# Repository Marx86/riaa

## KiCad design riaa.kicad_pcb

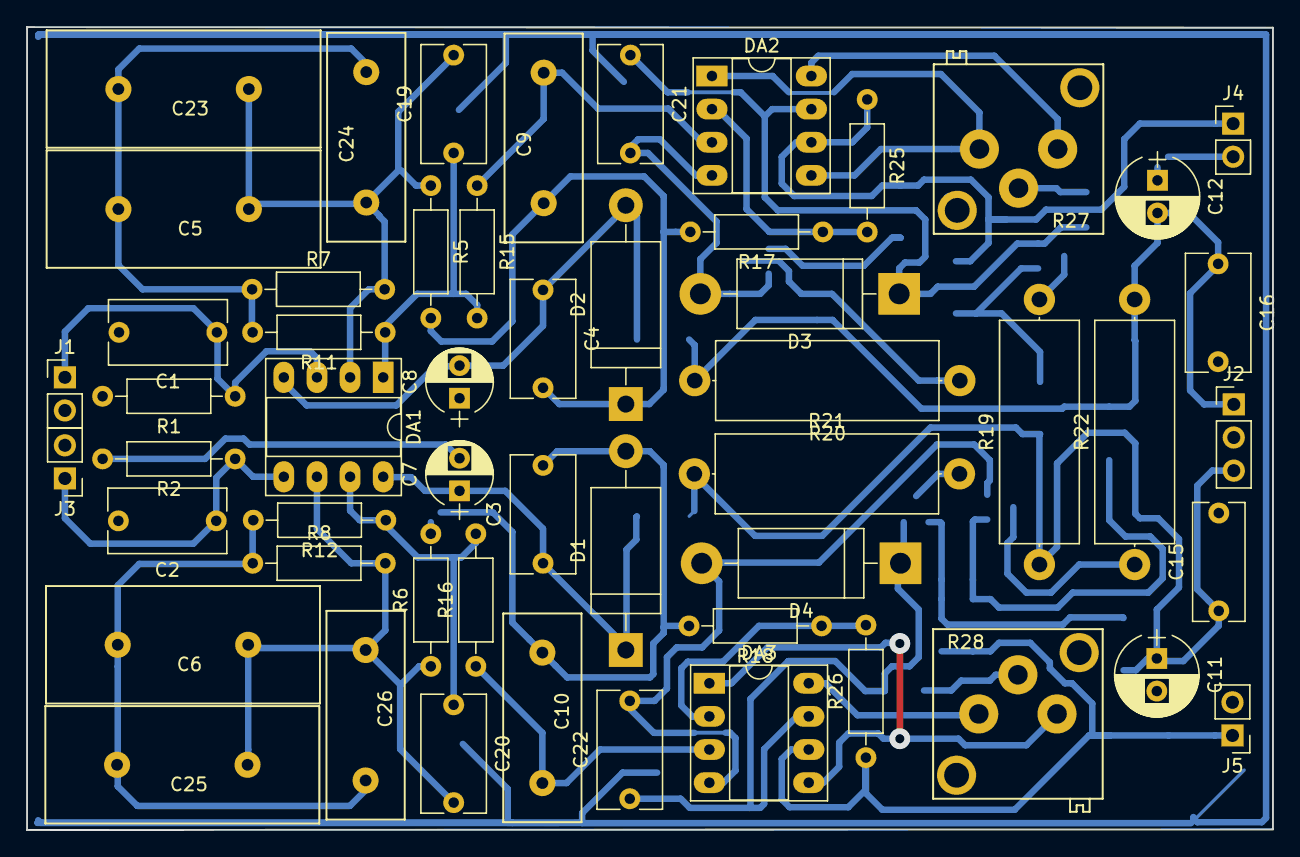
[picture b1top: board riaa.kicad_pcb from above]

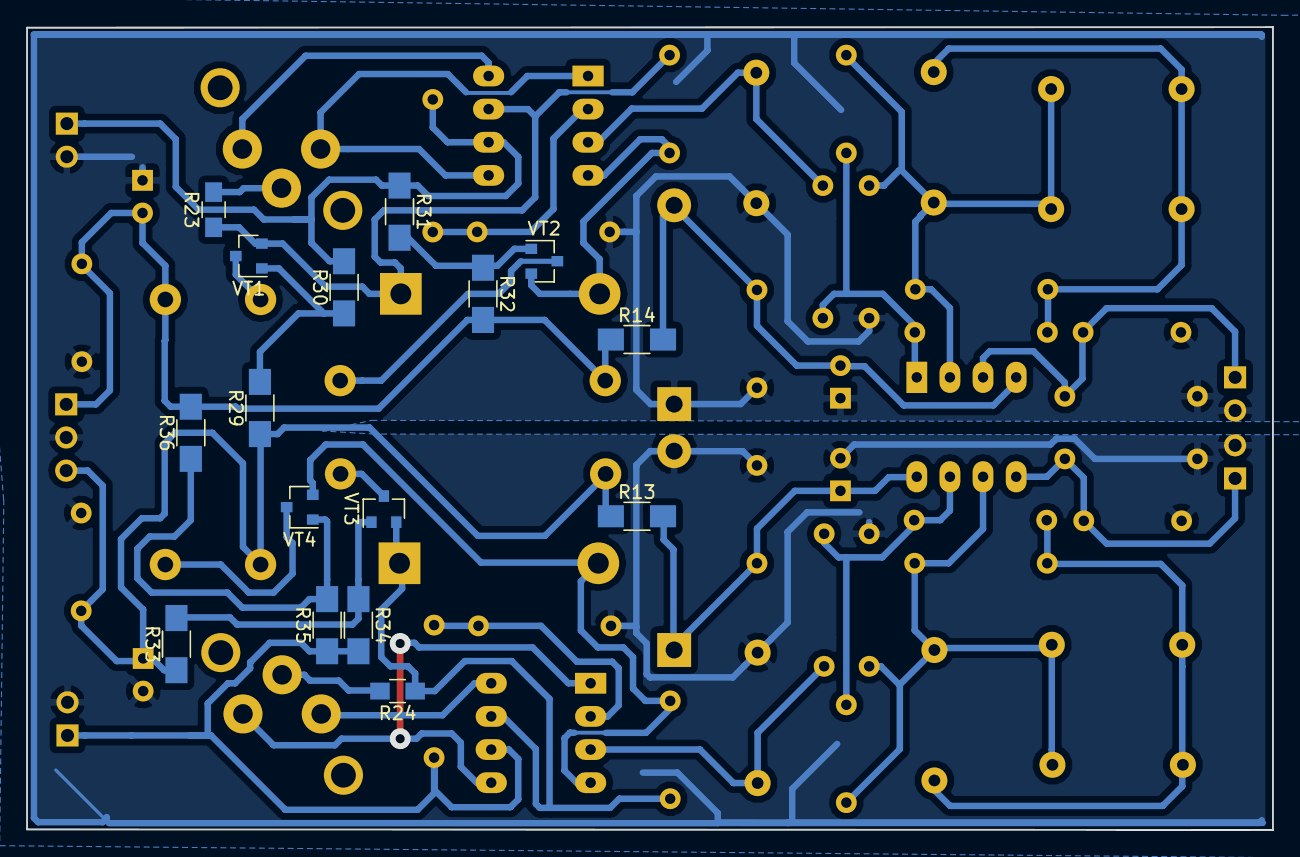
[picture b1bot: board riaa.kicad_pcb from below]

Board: 2 copper layers, 95.5 x 61.5 mm, 70 parts (16 on the bottom side), 37 nets.

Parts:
C1, C2: 200p; C_Rect_L9.0mm_W4.9mm_P7.50mm_MKT
C3, C4, C16, C21, C22: 0.1; C_Rect_L9.0mm_W4.9mm_P7.50mm_MKT
C5, C23, C25: 30.1n; k71-7_21x9_mm
C6: 30.2n; k71-7_21x9_mm
C7, C8: 2.2; CP_Radial_D5.0mm_P2.50mm
C9, C10: 10.75n; k71-7_16x6_mm
C11, C12: 2.2; CP_Radial_D6.3mm_P2.50mm
C15: 0.1; C_Rect_L9.0mm_W3.9mm_P7.50mm_MKT
C19, C20: 110; C_Rect_L9.0mm_W4.9mm_P7.50mm_MKT
C24, C26: 6510; k71-7_16x6_mm
D1, D2: КС518; D_DO-201_P15.24mm_Horizontal
D3, D4: 1N5364; D_DO-201AD_P15.24mm_Horizontal
DA1: OPA2132; DIP-8_W7.62mm_Socket_LongPads
DA2, DA3: AD845; DIP-8_W7.62mm_Socket_LongPads
J1, J3: IN; Pin_Header_Straight_1x02_Pitch2.54mm
J2: POWER; Pin_Header_Straight_1x03_Pitch2.54mm
J4, J5: OUT; Pin_Header_Straight_1x02_Pitch2.54mm
R1, R2: 47k; R_Axial_DIN0207_L6.3mm_D2.5mm_P10.16mm_Horizontal
R5, R6: 205; R_Axial_DIN0207_L6.3mm_D2.5mm_P10.16mm_Horizontal
R7, R8: 47.5k; R_Axial_DIN0207_L6.3mm_D2.5mm_P10.16mm_Horizontal
R11, R12: 5.11k; R_Axial_DIN0207_L6.3mm_D2.5mm_P10.16mm_Horizontal
R13, R14: 3.6k; R_1206_HandSoldering
R15, R16: 6.98k; R_Axial_DIN0207_L6.3mm_D2.5mm_P10.16mm_Horizontal
R17, R18: 10k; R_Axial_DIN0207_L6.3mm_D2.5mm_P10.16mm_Horizontal
R19, R20, R21, R22: 1.2k; R_Axial_DIN0617_L17.0mm_D6.0mm_P20.32mm_Horizontal
R23, R24: 390; R_0805_HandSoldering
R25, R26: 30k; R_Axial_DIN0207_L6.3mm_D2.5mm_P10.16mm_Horizontal
R27, R28: 1k; c5-2
R29, R32, R33, R36: 100k; R_1206_HandSoldering
R30, R31, R34, R35: 62k; R_1206_HandSoldering
VT1, VT3: MMBT5551; SOT-23
VT2, VT4: MMBT5401; SOT-23

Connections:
GNDA: C1.2, C2.2, C3.2, C4.2, C7.2, C8.1, C9.2, C10.2, C11.2, C12.1, C15.2, C16.2, D1.2, D2.1, J1.2, J2.2, J3.2, J4.2, J5.2, R1.2, R2.2, R5.2, R6.2, R17.2, R18.2
unnamed: C1.1, DA1.3, J1.1, R1.1
unnamed: C2.1, DA1.5, J3.1, R2.1
unnamed: C3.1, C7.1, D1.1, DA1.8, R13.2
unnamed: C4.1, C8.2, D2.2, DA1.4, R14.2
unnamed: C9.1, DA2.3, R15.1
unnamed: C10.1, DA3.3, R16.1
unnamed: C19.1, DA1.1, R11.1, R15.2
unnamed: C5.2, C19.2, C23.2, C24.2, DA1.2, R5.1, R7.2
unnamed: C20.1, DA1.7, R12.1, R16.2
unnamed: C6.2, C20.2, C25.2, C26.2, DA1.6, R6.1, R8.2
unnamed: C21.1, D3.1, DA2.7, R23.1, VT1.2
unnamed: C21.2, D3.2, DA2.4, VT2.2
unnamed: C22.1, D4.1, DA3.7, R24.1, VT3.2
unnamed: C22.2, D4.2, DA3.4, VT4.2
unnamed: C5.1, C23.1, C24.1, R7.1, R11.2
unnamed: C6.1, C25.1, C26.1, R8.1, R12.2
unnamed: DA2.1, DA2.5, R27.3
unnamed: DA2.2, R17.1, R25.2
unnamed: DA2.6, J4.1, R25.1, R30.2, R31.1
unnamed: DA2.8, R27.1
unnamed: DA3.1, DA3.5, R28.3
unnamed: DA3.2, R18.1, R26.2
unnamed: DA3.6, J5.1, R26.1, R34.2, R35.1
unnamed: DA3.8, R28.1
unnamed: R19.2, VT1.3
unnamed: R20.1, VT2.3
unnamed: R21.2, VT3.3
unnamed: R22.1, VT4.3
unnamed: R23.2, R27.2
unnamed: R24.2, R28.2
unnamed: R29.2, R30.1, VT1.1
unnamed: R31.2, R32.1, VT2.1
unnamed: R33.2, R34.1, VT3.1
unnamed: R35.2, R36.1, VT4.1
VCC: C11.1, C15.1, J2.3, R13.1, R19.1, R21.1, R29.1, R33.1
VEE: C12.2, C16.1, J2.1, R14.1, R20.2, R22.2, R32.2, R36.2

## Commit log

2019-05-31 Add circuit
2019-06-04 Change correction circuit
2019-06-05 Add K71-7 footprints
2019-06-06 Add c5-2 footprint
2019-06-18 Fix resistors
2019-06-26 Fix PCB
